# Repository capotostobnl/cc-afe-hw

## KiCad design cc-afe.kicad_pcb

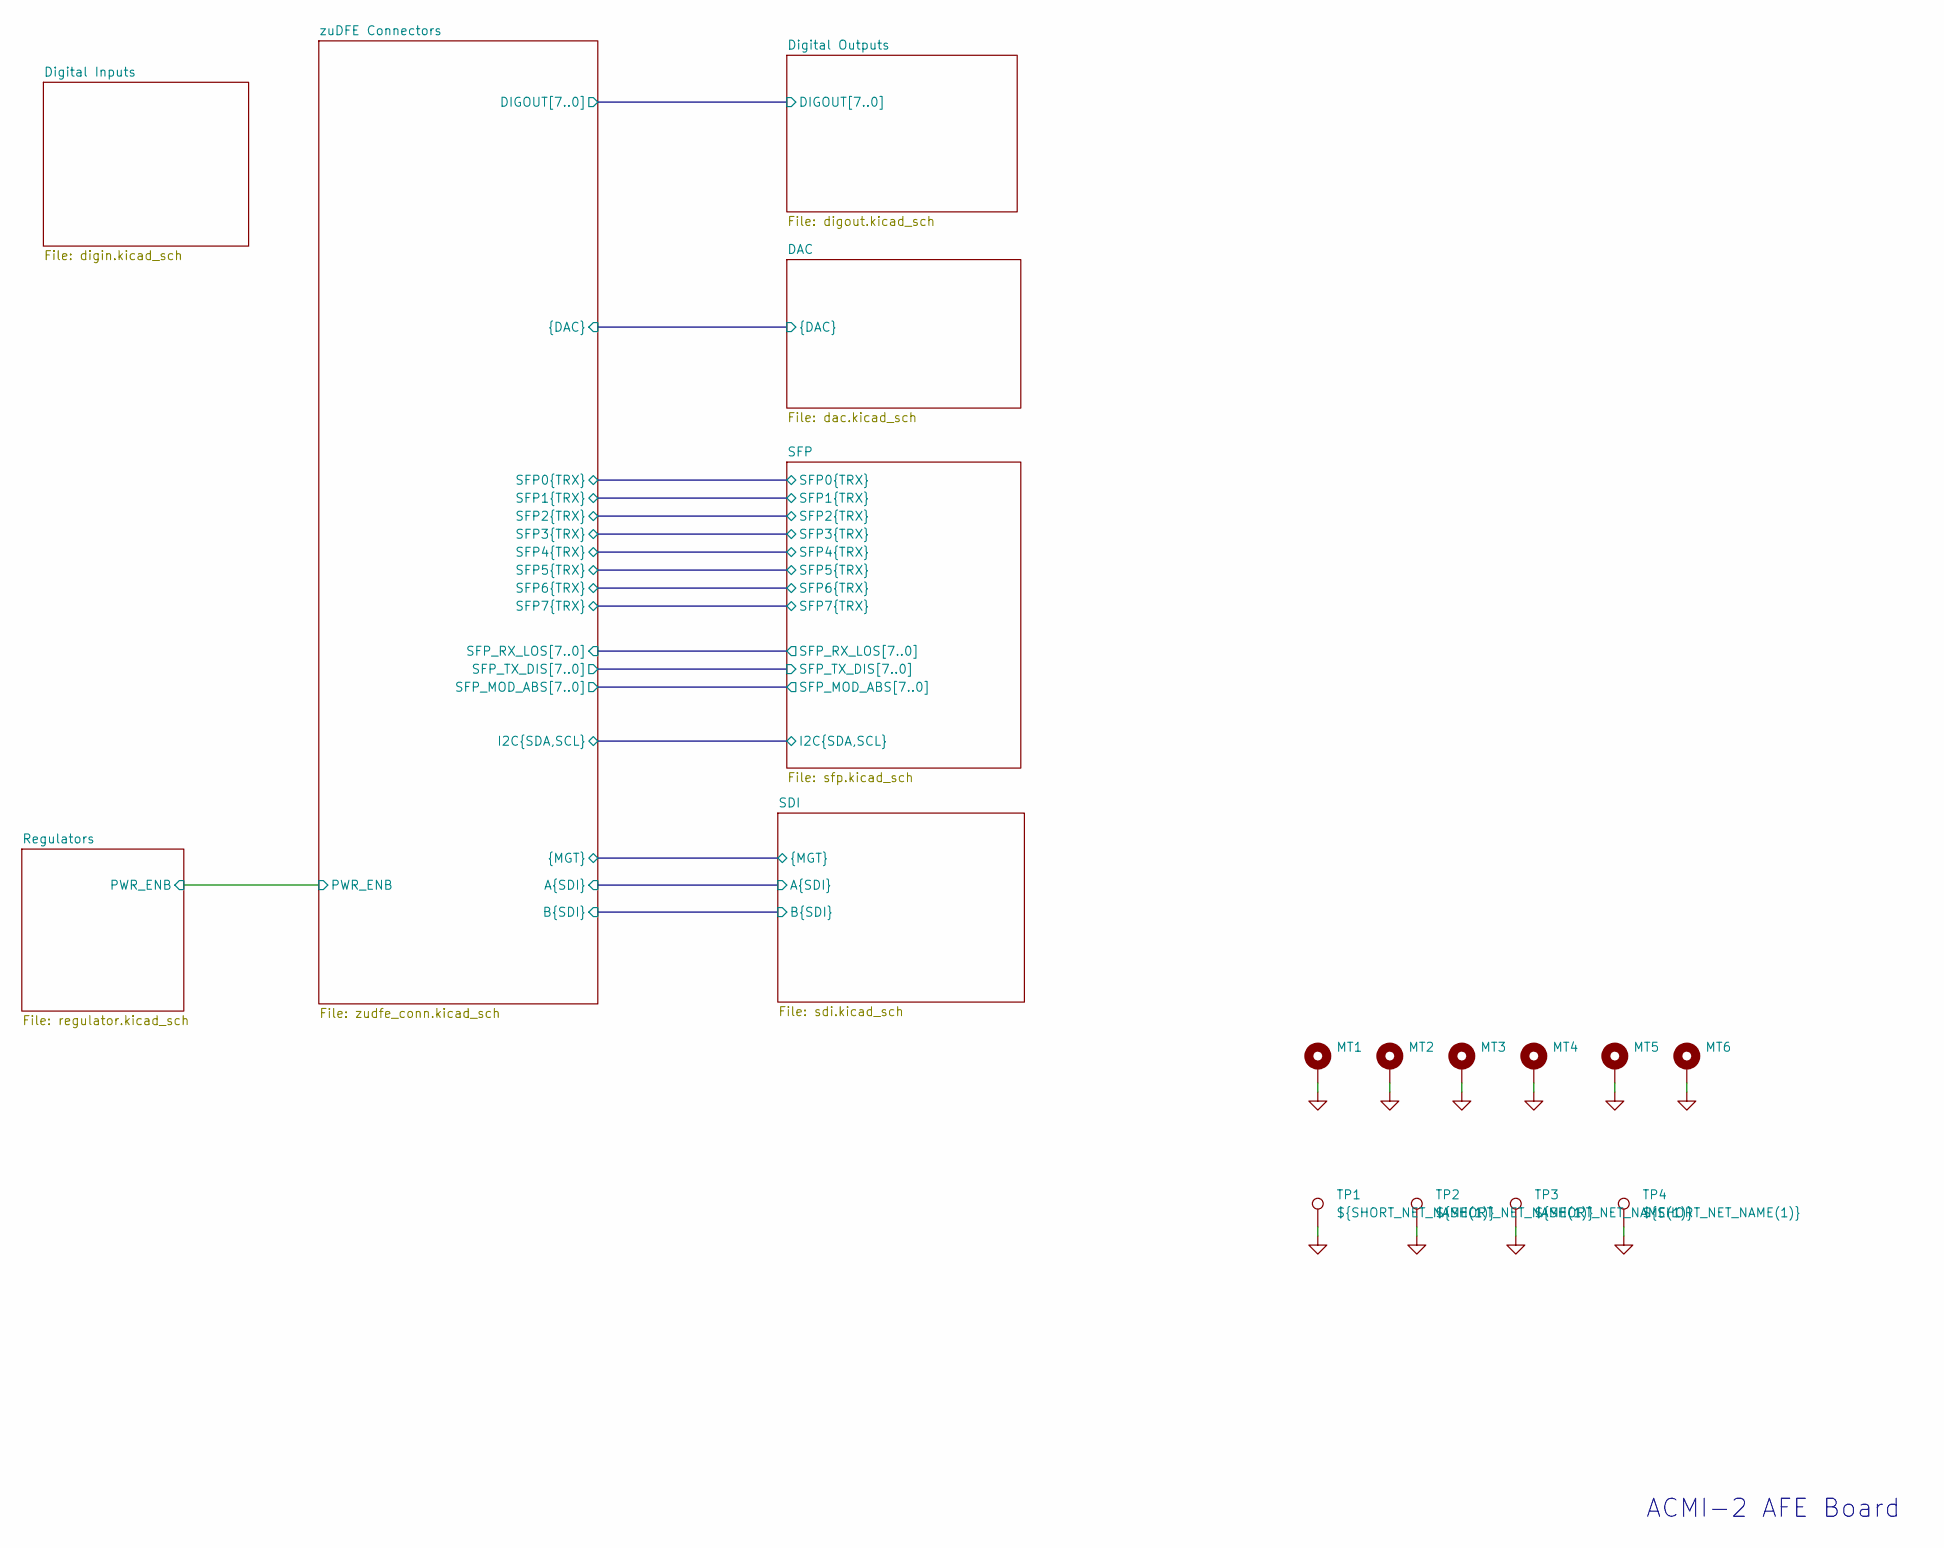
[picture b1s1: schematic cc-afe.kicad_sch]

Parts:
MT1, MT2, MT3, MT4, MT5, MT6: MountingHole_Pad; MountingHole_4.3mm_M4_DIN965_Pad
TP1, TP2, TP3, TP4: ${SHORT_NET_NAME(1)}; TestPoint_RCS-0C; MFG_PN RCS-0C

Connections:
GND: MT1.1, MT2.1, MT3.1, MT4.1, MT5.1, MT6.1, TP1.1, TP2.1, TP3.1, TP4.1; also elsewhere on the board

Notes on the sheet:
ACMI-2 AFE Board

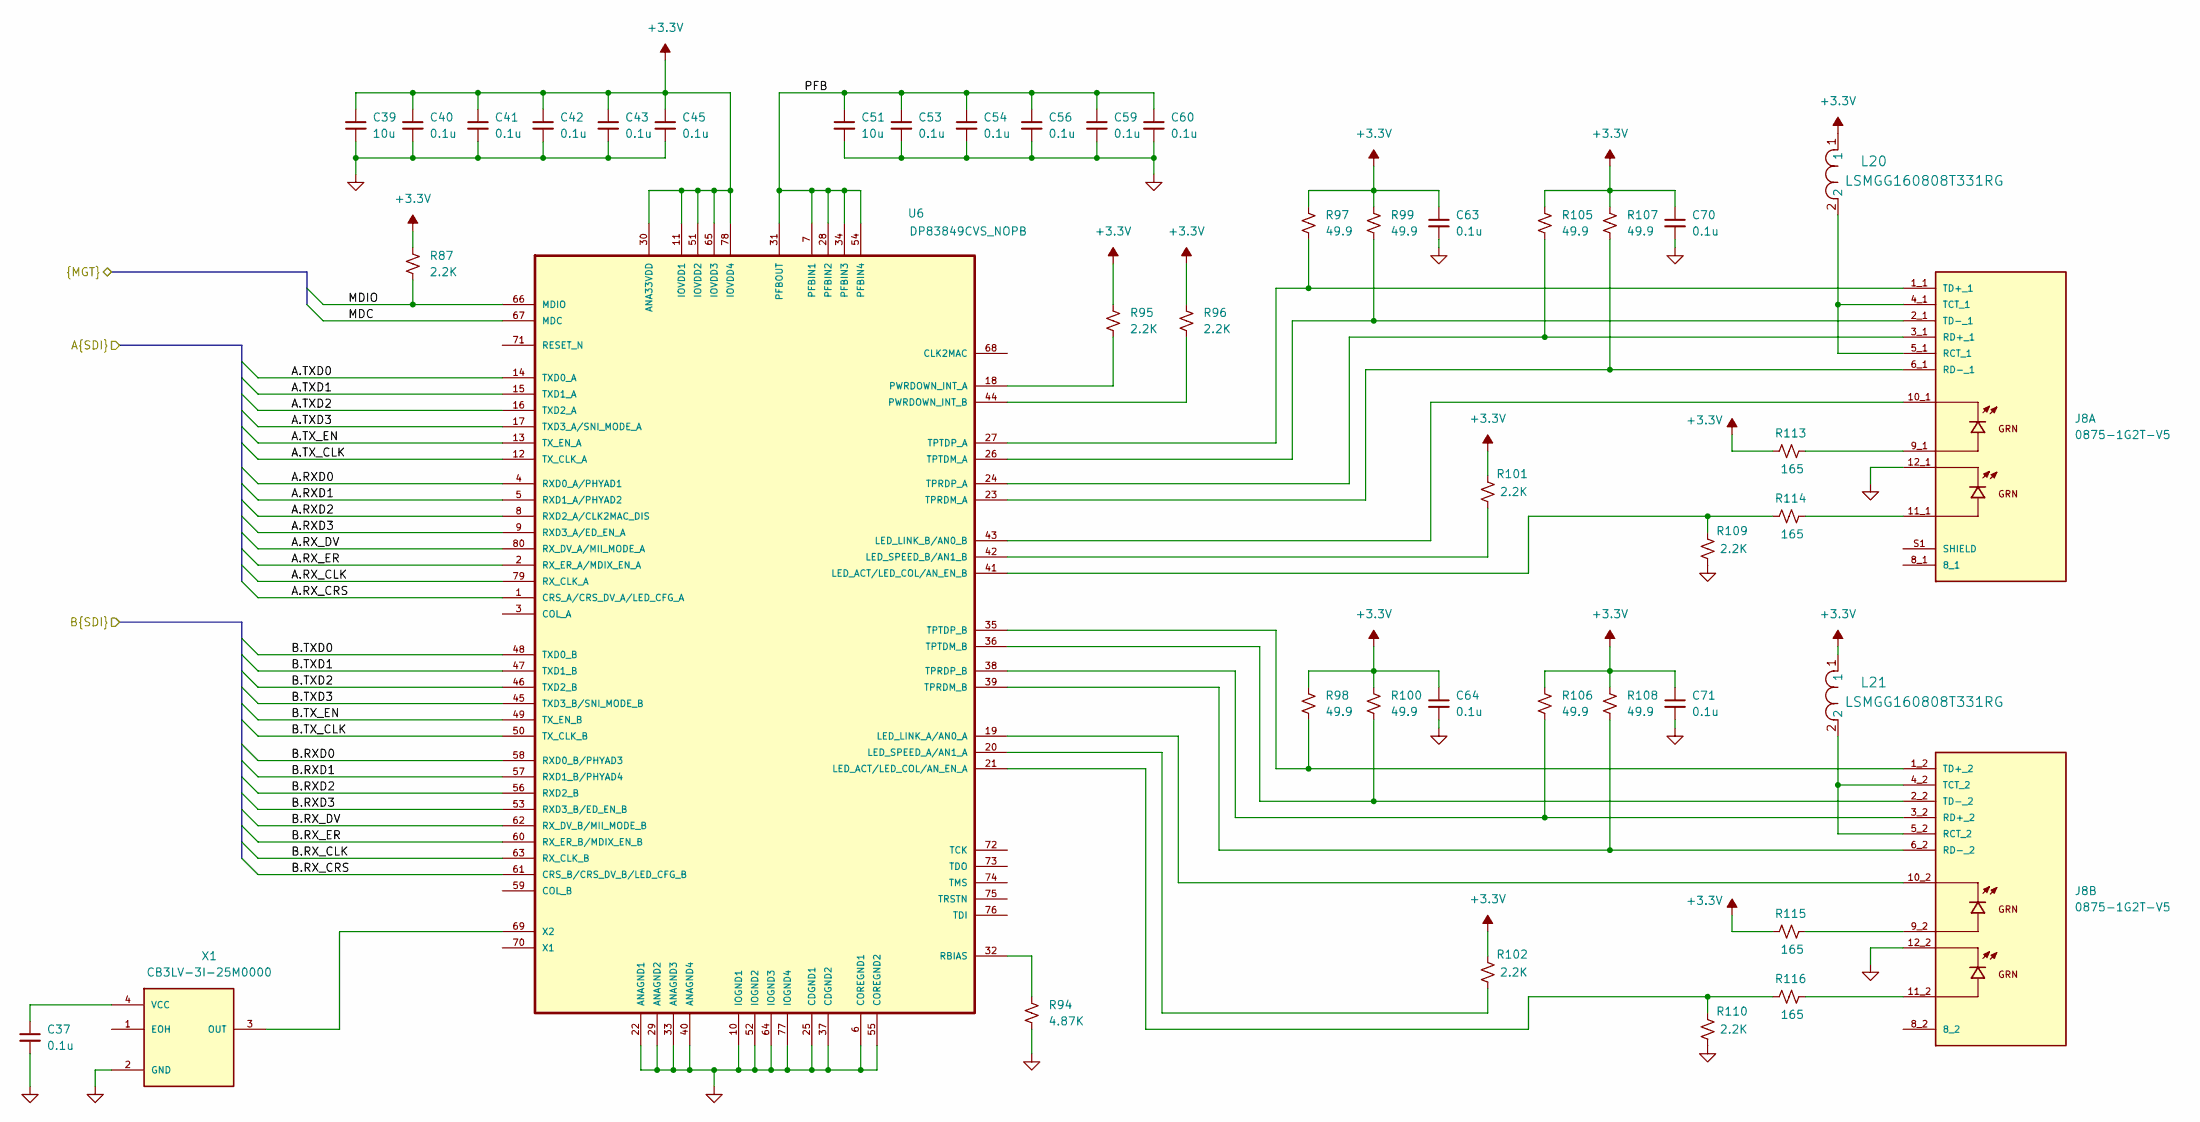
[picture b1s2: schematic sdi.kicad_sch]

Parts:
C37, C40, C41, C42, C43, C45, C53, C54, C56, C59, C60, C63, C64, C70, C71: 0.1u; C_0603_1608Metric; Voltage 50; MFG_PN GCJ188R71H104KA12D
C39, C51: 10u; C_0805_2012Metric; MFG_PN GRM21BR61C106KE15K
J8: 0875-1G2T-V5; BEL_0875-1G2T-V5
L20, L21: LSMGG160808T331RG; IND_LSMG_160808_TAY; MFG_PN LSMGG160808T331RG
R87, R95, R96: 2.2K; R_0603_1608Metric; MFG_PN ERJ-3EKF49R9V
R94: 4.87K; R_0603_1608Metric
R97, R98, R99, R100, R105, R106, R107, R108: 49.9; R_0603_1608Metric; MFG_PN ERJ-3EKF49R9V
R101, R102, R109, R110: 2.2K; R_0603_1608Metric
R113, R114, R115, R116: 165; R_0603_1608Metric
U6: DP83849CVS_NOPB; QFP50P1400X1400X120-80N; MFG_PN DP83849CVS/NOPB
X1: CB3LV-3I-25M0000; OSCCC700X500X180-4N; MFG_PN CB3LV-3I-25M0000

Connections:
+3.3V: C39.1, C40.1, C41.1, C42.1, C43.1, C45.1, C63.1, C64.1, C70.1, C71.1, L20.1, L21.1, R87.1, R95.1, R96.1, R97.1, R98.1, R99.1, R100.1, R101.2, R102.2, R105.1, R106.1, R107.1, R108.1, R113.1, R115.1, U6.11 (IOVDD1), U6.30 (ANA33VDD), U6.51 (IOVDD2), U6.65 (IOVDD3), U6.78 (IOVDD4); also elsewhere on the board
/SDI/A.RXD0: U6.4 (RXD0_A/PHYAD1); also elsewhere on the board
/SDI/A.RXD1: U6.5 (RXD1_A/PHYAD2); also elsewhere on the board
/SDI/A.RXD2: U6.8 (RXD2_A/CLK2MAC_DIS); also elsewhere on the board
/SDI/A.RXD3: U6.9 (RXD3_A/ED_EN_A); also elsewhere on the board
/SDI/A.RX_CLK: U6.79 (RX_CLK_A); also elsewhere on the board
/SDI/A.RX_CRS: U6.1 (CRS_A/CRS_DV_A/LED_CFG_A); also elsewhere on the board
/SDI/A.RX_DV: U6.80 (RX_DV_A/MII_MODE_A); also elsewhere on the board
/SDI/A.RX_ER: U6.2 (RX_ER_A/MDIX_EN_A); also elsewhere on the board
/SDI/A.TXD0: U6.14 (TXD0_A); also elsewhere on the board
/SDI/A.TXD1: U6.15 (TXD1_A); also elsewhere on the board
/SDI/A.TXD2: U6.16 (TXD2_A); also elsewhere on the board
/SDI/A.TXD3: U6.17 (TXD3_A/SNI_MODE_A); also elsewhere on the board
/SDI/A.TX_CLK: U6.12 (TX_CLK_A); also elsewhere on the board
/SDI/A.TX_EN: U6.13 (TX_EN_A); also elsewhere on the board
/SDI/B.RXD0: U6.58 (RXD0_B/PHYAD3); also elsewhere on the board
/SDI/B.RXD1: U6.57 (RXD1_B/PHYAD4); also elsewhere on the board
/SDI/B.RXD2: U6.56 (RXD2_B); also elsewhere on the board
/SDI/B.RXD3: U6.53 (RXD3_B/ED_EN_B); also elsewhere on the board
/SDI/B.RX_CLK: U6.63 (RX_CLK_B); also elsewhere on the board
/SDI/B.RX_CRS: U6.61 (CRS_B/CRS_DV_B/LED_CFG_B); also elsewhere on the board
/SDI/B.RX_DV: U6.62 (RX_DV_B/MII_MODE_B); also elsewhere on the board
/SDI/B.RX_ER: U6.60 (RX_ER_B/MDIX_EN_B); also elsewhere on the board
/SDI/B.TXD0: U6.48 (TXD0_B); also elsewhere on the board
/SDI/B.TXD1: U6.47 (TXD1_B); also elsewhere on the board
/SDI/B.TXD2: U6.46 (TXD2_B); also elsewhere on the board
/SDI/B.TXD3: U6.45 (TXD3_B/SNI_MODE_B); also elsewhere on the board
/SDI/B.TX_CLK: U6.50 (TX_CLK_B); also elsewhere on the board
/SDI/B.TX_EN: U6.49 (TX_EN_B); also elsewhere on the board
/SDI/MDC: U6.67 (MDC); also elsewhere on the board
/SDI/MDIO: R87.2, U6.66 (MDIO); also elsewhere on the board
/SDI/PFB: C51.1, C53.1, C54.1, C56.1, C59.1, C60.1, U6.7 (PFBIN1), U6.28 (PFBIN2), U6.31 (PFBOUT), U6.34 (PFBIN3), U6.54 (PFBIN4)
GND: C37.2, C39.2, C40.2, C41.2, C42.2, C43.2, C45.2, C51.2, C53.2, C54.2, C56.2, C59.2, C60.2, C63.2, C64.2, C70.2, C71.2, J8.12_1, J8.12_2, R94.2, R109.1, R110.1, U6.6 (COREGND1), U6.10 (IOGND1), U6.22 (ANAGND1), U6.25 (CDGND1), U6.29 (ANAGND2), U6.33 (ANAGND3), U6.37 (CDGND2), U6.40 (ANAGND4), U6.52 (IOGND2), U6.55 (COREGND2), U6.64 (IOGND3), U6.77 (IOGND4), X1.2 (GND); also elsewhere on the board
unnamed: J8.9_1, R113.2
unnamed: J8.9_2, R115.2
unnamed: J8.11_1, R114.2
unnamed: J8.11_2, R116.2
unnamed: J8.4_1 (TCT_1), J8.5_1 (RCT_1), L20.2
unnamed: J8.3_1 (RD+_1), R105.2, U6.24 (TPRDP_A)
unnamed: J8.6_1 (RD-_1), R107.2, U6.23 (TPRDM_A)
unnamed: J8.S1 (SHIELD), J8.S2 (SHIELD), J8.S3 (SHIELD)
unnamed: J8.1_1 (TD+_1), R97.2, U6.27 (TPTDP_A)
unnamed: J8.2_1 (TD-_1), R99.2, U6.26 (TPTDM_A)
unnamed: J8.4_2 (TCT_2), J8.5_2 (RCT_2), L21.2
unnamed: J8.3_2 (RD+_2), R106.2, U6.38 (TPRDP_B)
unnamed: J8.6_2 (RD-_2), R108.2, U6.39 (TPRDM_B)
unnamed: J8.1_2 (TD+_2), R98.2, U6.35 (TPTDP_B)
unnamed: J8.2_2 (TD-_2), R100.2, U6.36 (TPTDM_B)
unnamed: R110.2, R116.1, U6.21 (LED_ACT/LED_COL/AN_EN_A)
unnamed: R109.2, R114.1, U6.41 (LED_ACT/LED_COL/AN_EN_B)
unnamed: J8.10_2, U6.19 (LED_LINK_A/AN0_A)
unnamed: J8.10_1, U6.43 (LED_LINK_B/AN0_B)
unnamed: R102.1, U6.20 (LED_SPEED_A/AN1_A)
unnamed: R101.1, U6.42 (LED_SPEED_B/AN1_B)
unnamed: R95.2, U6.18 (PWRDOWN_INT_A)
unnamed: R96.2, U6.44 (PWRDOWN_INT_B)
unnamed: R94.1, U6.32 (RBIAS)
unnamed: U6.69 (X2), X1.3 (OUT)
unnamed: C37.1, X1.4 (VCC)

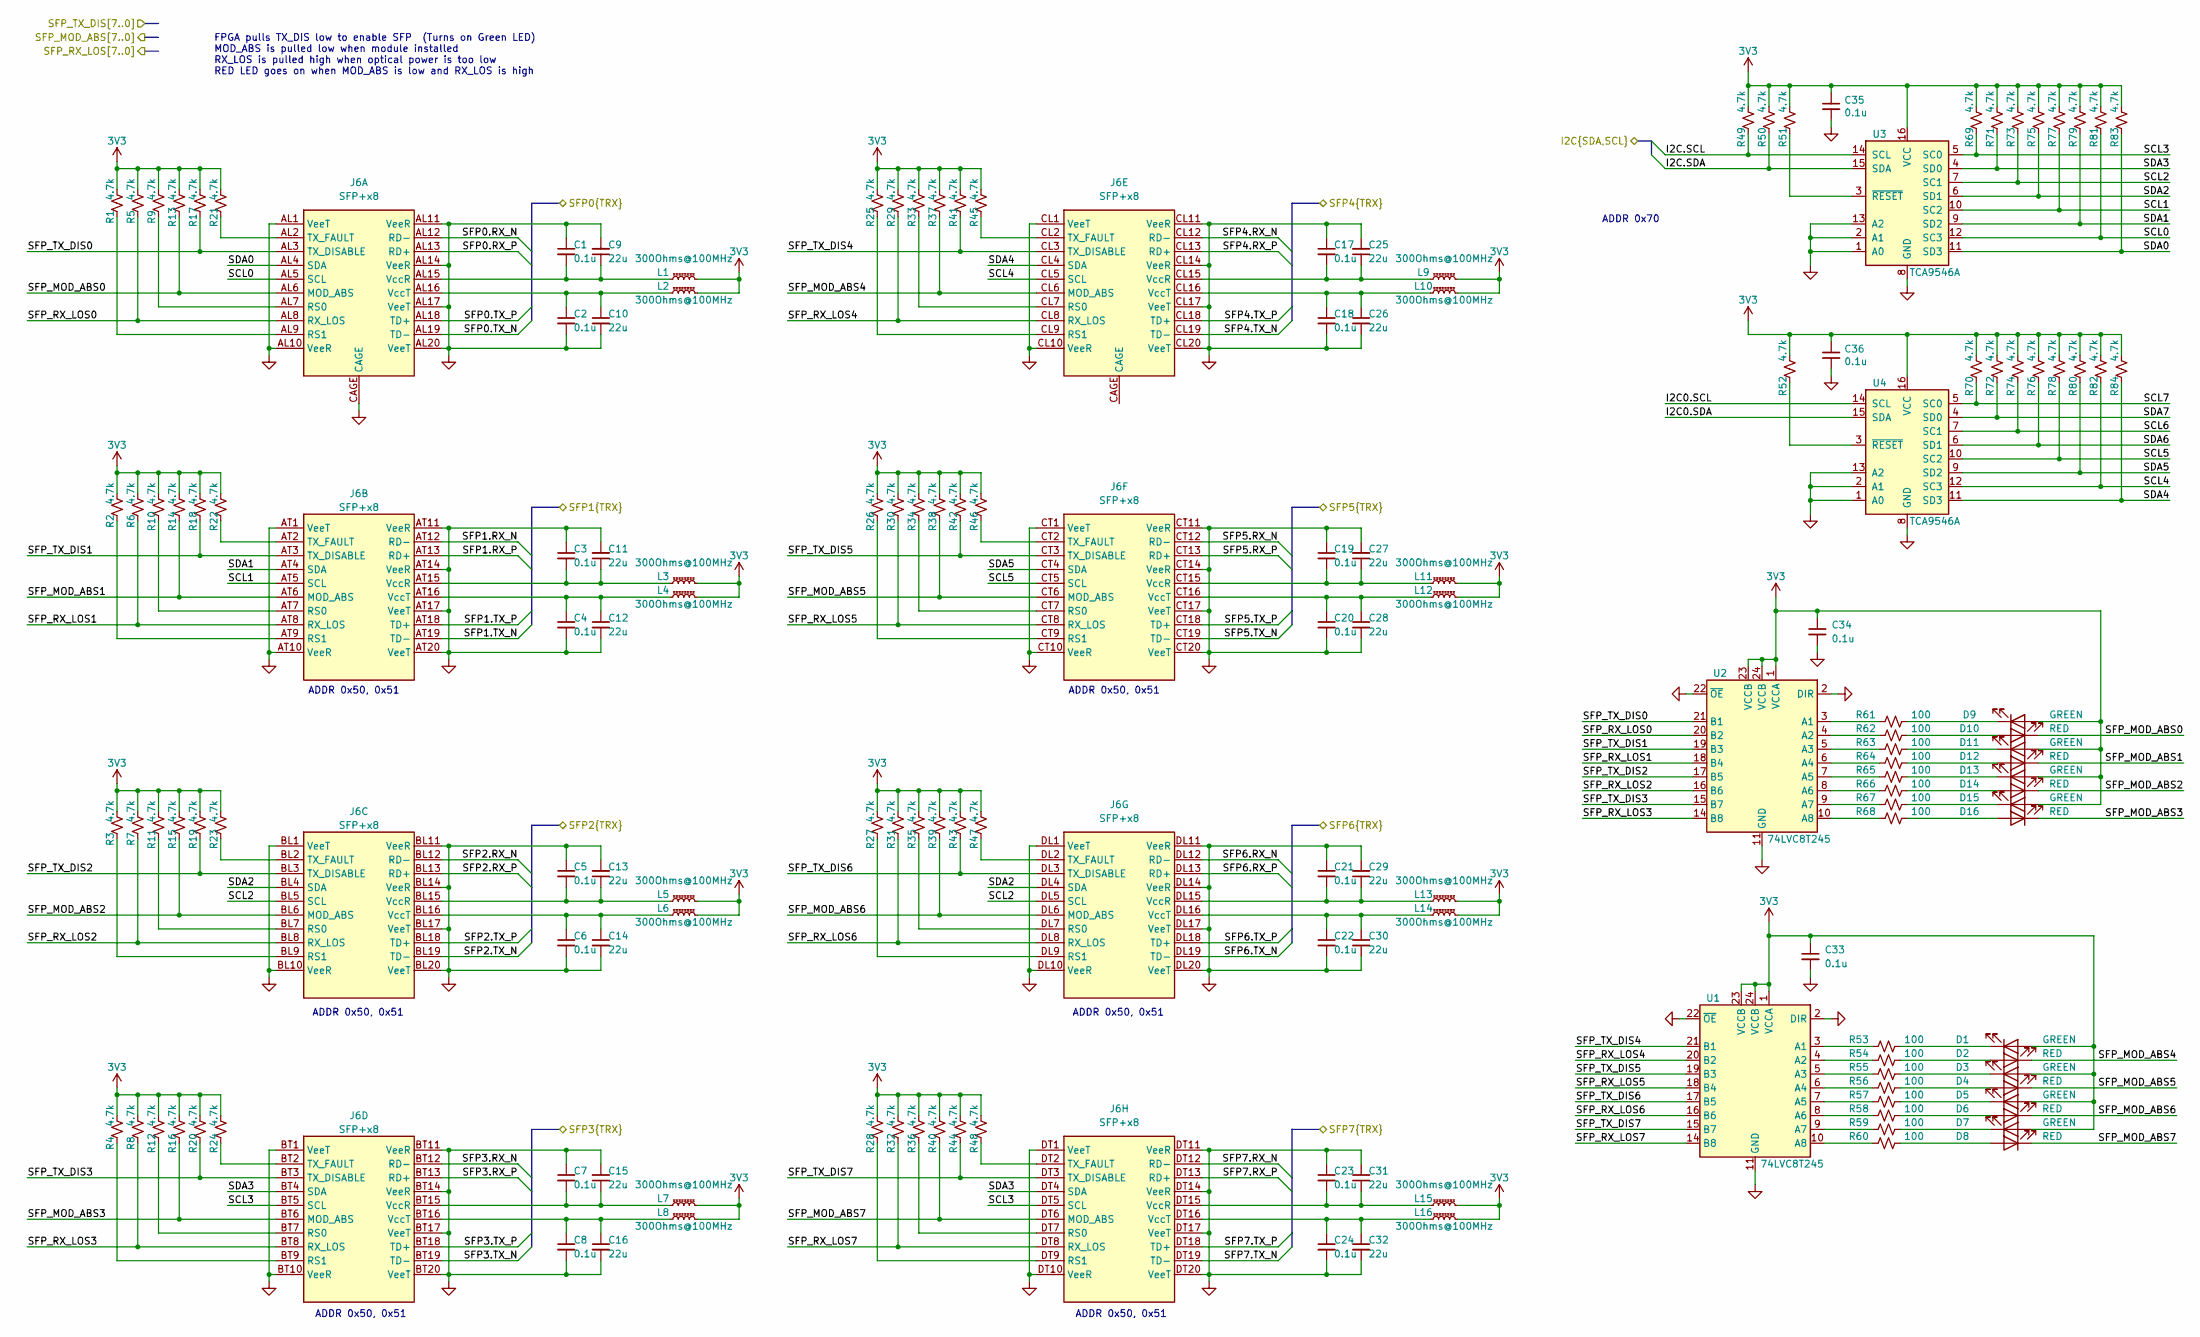
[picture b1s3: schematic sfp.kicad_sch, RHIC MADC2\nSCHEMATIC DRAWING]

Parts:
C1, C2, C3, C4, C5, C6, C7, C8, C17, C18, C19, C20, C21, C22, C23, C24, C33, C34, C35, C36: 0.1u; C_0603_1608Metric; MFG_PN CL10B104KB8NNNC
C9, C10, C11, C12, C13, C14, C15, C16, C25, C26, C27, C28, C29, C30, C31, C32: 22u; C_0805_2012Metric; MFG_PN CL21A226MAYNNNE
D1, D3, D5, D7, D9, D11, D13, D15: GREEN; LED_0603_1608Metric; MFG_PN LTST-C191KGKT
D2, D4, D6, D8, D10, D12, D14, D16: RED; LED_0603_1608Metric; MFG_PN LTST-C191KRKT
J6: SFP+x8; 1-2007394-5
L1, L2, L3, L4, L5, L6, L7, L8, L9, L10, L11, L12, L13, L14, L15, L16: 300Ohms@100MHz; L_0603_1608Metric; MFG_PN 742792641
R1, R2, R3, R4, R5, R6, R7, R8, R9, R10, R11, R12, R13, R14, R15, R16, R17, R18, R19, R20, R21, R22, R23, R24, R25, R26, R27, R28, R29, R30, R31, R32, R33, R34, R35, R36, R37, R38, R39, R40, R41, R42, R43, R44, R45, R46, R47, R48, R49, R50, R51, R52, R69, R70, R71, R72, R73, R74, R75, R76, R77, R78, R79, R80, R81, R82, R83, R84: 4.7k; R_0603_1608Metric; MFG_PN RMCF0603FT4K70
R53, R54, R55, R56, R57, R58, R59, R60, R61, R62, R63, R64, R65, R66, R67, R68: 100; R_0603_1608Metric; MFG_PN RMCF0603FT100R
U1, U2: 74LVC8T245; TSSOP-24_4.4x7.8mm_P0.65mm; MFG_PN 74LVC8T245PW,118
U3, U4: TCA9546A; TSSOP-16_4.4x5mm_P0.65mm; MFG_PN TCA9546APWR

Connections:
3V3: C33.1, C34.1, C35.1, C36.1, D1.2 (A), D3.2 (A), D5.2 (A), D7.2 (A), D9.2 (A), D11.2 (A), D13.2 (A), D15.2 (A), L1.1, L2.1, L3.1, L4.1, L5.1, L6.1, L7.1, L8.1, L9.1, L10.1, L11.1, L12.1, L13.1, L14.1, L15.1, L16.1, R1.2, R2.2, R3.2, R4.2, R5.2, R6.2, R7.2, R8.2, R9.2, R10.2, R11.2, R12.2, R13.2, R14.2, R15.2, R16.2, R17.2, R18.2, R19.2, R20.2, R21.2, R22.2, R23.2, R24.2, R25.2, R26.2, R27.2, R28.2, R29.2, R30.2, R31.2, R32.2, R33.2, R34.2, R35.2, R36.2, R37.2, R38.2, R39.2, R40.2, R41.2, R42.2, R43.2, R44.2, R45.2, R46.2, R47.2, R48.2, R49.1, R50.1, R51.1, R52.1, R69.1, R70.1, R71.1, R72.1, R73.1, R74.1, R75.1, R76.1, R77.1, R78.1, R79.1, R80.1, R81.1, R82.1, R83.1, R84.1, U1.1 (VCCA), U1.23 (VCCB), U1.24 (VCCB), U2.1 (VCCA), U2.23 (VCCB), U2.24 (VCCB), U3.16 (VCC), U4.16 (VCC)
/SFP/I2C0.SCL: U4.14 (SCL)
/SFP/I2C0.SDA: U4.15 (SDA)
/SFP/I2C.SCL: R49.2, U3.14 (SCL); also elsewhere on the board
/SFP/I2C.SDA: R50.2, U3.15 (SDA); also elsewhere on the board
/SFP/SCL0: J6.AL5 (SCL), R81.2, U3.12 (SC3)
/SFP/SCL1: J6.AT5 (SCL), R77.2, U3.10 (SC2)
/SFP/SCL2: J6.BL5 (SCL), J6.DL5 (SCL), R73.2, U3.7 (SC1)
/SFP/SCL3: J6.BT5 (SCL), J6.DT5 (SCL), R69.2, U3.5 (SC0)
/SFP/SCL4: J6.CL5 (SCL), R82.2, U4.12 (SC3)
/SFP/SCL5: J6.CT5 (SCL), R78.2, U4.10 (SC2)
/SFP/SCL6: R74.2, U4.7 (SC1)
/SFP/SCL7: R70.2, U4.5 (SC0)
/SFP/SDA0: J6.AL4 (SDA), R83.2, U3.11 (SD3)
/SFP/SDA1: J6.AT4 (SDA), R79.2, U3.9 (SD2)
/SFP/SDA2: J6.BL4 (SDA), J6.DL4 (SDA), R75.2, U3.6 (SD1)
/SFP/SDA3: J6.BT4 (SDA), J6.DT4 (SDA), R71.2, U3.4 (SD0)
/SFP/SDA4: J6.CL4 (SDA), R84.2, U4.11 (SD3)
/SFP/SDA5: J6.CT4 (SDA), R80.2, U4.9 (SD2)
/SFP/SDA6: R76.2, U4.6 (SD1)
/SFP/SDA7: R72.2, U4.4 (SD0)
/SFP/SFP0.RX_N: J6.AL12 (RD-); also elsewhere on the board
/SFP/SFP0.RX_P: J6.AL13 (RD+); also elsewhere on the board
/SFP/SFP0.TX_N: J6.AL19 (TD-); also elsewhere on the board
/SFP/SFP0.TX_P: J6.AL18 (TD+); also elsewhere on the board
/SFP/SFP1.RX_N: J6.AT12 (RD-); also elsewhere on the board
/SFP/SFP1.RX_P: J6.AT13 (RD+); also elsewhere on the board
/SFP/SFP1.TX_N: J6.AT19 (TD-); also elsewhere on the board
/SFP/SFP1.TX_P: J6.AT18 (TD+); also elsewhere on the board
/SFP/SFP2.RX_N: J6.BL12 (RD-); also elsewhere on the board
/SFP/SFP2.RX_P: J6.BL13 (RD+); also elsewhere on the board
/SFP/SFP2.TX_N: J6.BL19 (TD-); also elsewhere on the board
/SFP/SFP2.TX_P: J6.BL18 (TD+); also elsewhere on the board
/SFP/SFP3.RX_N: J6.BT12 (RD-); also elsewhere on the board
/SFP/SFP3.RX_P: J6.BT13 (RD+); also elsewhere on the board
/SFP/SFP3.TX_N: J6.BT19 (TD-); also elsewhere on the board
/SFP/SFP3.TX_P: J6.BT18 (TD+); also elsewhere on the board
/SFP/SFP4.RX_N: J6.CL12 (RD-); also elsewhere on the board
/SFP/SFP4.RX_P: J6.CL13 (RD+); also elsewhere on the board
/SFP/SFP4.TX_N: J6.CL19 (TD-); also elsewhere on the board
/SFP/SFP4.TX_P: J6.CL18 (TD+); also elsewhere on the board
/SFP/SFP5.RX_N: J6.CT12 (RD-); also elsewhere on the board
/SFP/SFP5.RX_P: J6.CT13 (RD+); also elsewhere on the board
/SFP/SFP5.TX_N: J6.CT19 (TD-); also elsewhere on the board
/SFP/SFP5.TX_P: J6.CT18 (TD+); also elsewhere on the board
/SFP/SFP6.RX_N: J6.DL12 (RD-); also elsewhere on the board
/SFP/SFP6.RX_P: J6.DL13 (RD+); also elsewhere on the board
/SFP/SFP6.TX_N: J6.DL19 (TD-); also elsewhere on the board
/SFP/SFP6.TX_P: J6.DL18 (TD+); also elsewhere on the board
/SFP/SFP7.RX_N: J6.DT12 (RD-); also elsewhere on the board
/SFP/SFP7.RX_P: J6.DT13 (RD+); also elsewhere on the board
/SFP/SFP7.TX_N: J6.DT19 (TD-); also elsewhere on the board
/SFP/SFP7.TX_P: J6.DT18 (TD+); also elsewhere on the board
/SFP/SFP_MOD_ABS0: D10.1 (K), J6.AL6 (MOD_ABS), R13.1; also elsewhere on the board
/SFP/SFP_MOD_ABS1: D12.1 (K), J6.AT6 (MOD_ABS), R14.1; also elsewhere on the board
/SFP/SFP_MOD_ABS2: D14.1 (K), J6.BL6 (MOD_ABS), R15.1; also elsewhere on the board
/SFP/SFP_MOD_ABS3: D16.1 (K), J6.BT6 (MOD_ABS), R16.1; also elsewhere on the board
/SFP/SFP_MOD_ABS4: D2.1 (K), J6.CL6 (MOD_ABS), R37.1; also elsewhere on the board
/SFP/SFP_MOD_ABS5: D4.1 (K), J6.CT6 (MOD_ABS), R38.1; also elsewhere on the board
/SFP/SFP_MOD_ABS6: D6.1 (K), J6.DL6 (MOD_ABS), R39.1; also elsewhere on the board
/SFP/SFP_MOD_ABS7: D8.1 (K), J6.DT6 (MOD_ABS), R40.1; also elsewhere on the board
/SFP/SFP_RX_LOS0: J6.AL8 (RX_LOS), R5.1, U2.20 (B2); also elsewhere on the board
/SFP/SFP_RX_LOS1: J6.AT8 (RX_LOS), R6.1, U2.18 (B4); also elsewhere on the board
/SFP/SFP_RX_LOS2: J6.BL8 (RX_LOS), R7.1, U2.16 (B6); also elsewhere on the board
/SFP/SFP_RX_LOS3: J6.BT8 (RX_LOS), R8.1, U2.14 (B8); also elsewhere on the board
/SFP/SFP_RX_LOS4: J6.CL8 (RX_LOS), R29.1, U1.20 (B2); also elsewhere on the board
/SFP/SFP_RX_LOS5: J6.CT8 (RX_LOS), R30.1, U1.18 (B4); also elsewhere on the board
/SFP/SFP_RX_LOS6: J6.DL8 (RX_LOS), R31.1, U1.16 (B6); also elsewhere on the board
/SFP/SFP_RX_LOS7: J6.DT8 (RX_LOS), R32.1, U1.14 (B8); also elsewhere on the board
/SFP/SFP_TX_DIS0: J6.AL3 (TX_DISABLE), R17.1, U2.21 (B1); also elsewhere on the board
/SFP/SFP_TX_DIS1: J6.AT3 (TX_DISABLE), R18.1, U2.19 (B3); also elsewhere on the board
/SFP/SFP_TX_DIS2: J6.BL3 (TX_DISABLE), R19.1, U2.17 (B5); also elsewhere on the board
/SFP/SFP_TX_DIS3: J6.BT3 (TX_DISABLE), R20.1, U2.15 (B7); also elsewhere on the board
/SFP/SFP_TX_DIS4: J6.CL3 (TX_DISABLE), R41.1, U1.21 (B1); also elsewhere on the board
/SFP/SFP_TX_DIS5: J6.CT3 (TX_DISABLE), R42.1, U1.19 (B3); also elsewhere on the board
/SFP/SFP_TX_DIS6: J6.DL3 (TX_DISABLE), R43.1, U1.17 (B5); also elsewhere on the board
/SFP/SFP_TX_DIS7: J6.DT3 (TX_DISABLE), R44.1, U1.15 (B7); also elsewhere on the board
GND: C1.1, C2.2, C3.1, C4.2, C5.1, C6.2, C7.1, C8.2, C9.2, C10.2, C11.2, C12.2, C13.2, C14.2, C15.2, C16.2, C17.1, C18.2, C19.1, C20.2, C21.1, C22.2, C23.1, C24.2, C25.2, C26.2, C27.2, C28.2, C29.2, C30.2, C31.2, C32.2, C33.2, C34.2, C35.2, C36.2, J6.AL1 (VeeT), J6.AL10 (VeeR), J6.AL11 (VeeR), J6.AL14 (VeeR), J6.AL17 (VeeT), J6.AL20 (VeeT), J6.AT1 (VeeT), J6.AT10 (VeeR), J6.AT11 (VeeR), J6.AT14 (VeeR), J6.AT17 (VeeT), J6.AT20 (VeeT), J6.BL1 (VeeT), J6.BL10 (VeeR), J6.BL11 (VeeR), J6.BL14 (VeeR), J6.BL17 (VeeT), J6.BL20 (VeeT), J6.BT1 (VeeT), J6.BT10 (VeeR), J6.BT11 (VeeR), J6.BT14 (VeeR), J6.BT17 (VeeT), J6.BT20 (VeeT), J6.CAGE, J6.CL1 (VeeT), J6.CL10 (VeeR), J6.CL11 (VeeR), J6.CL14 (VeeR), J6.CL17 (VeeT), J6.CL20 (VeeT), J6.CT1 (VeeT), J6.CT10 (VeeR), J6.CT11 (VeeR), J6.CT14 (VeeR), J6.CT17 (VeeT), J6.CT20 (VeeT), J6.DL1 (VeeT), J6.DL10 (VeeR), J6.DL11 (VeeR), J6.DL14 (VeeR), J6.DL17 (VeeT), J6.DL20 (VeeT), J6.DT1 (VeeT), J6.DT10 (VeeR), J6.DT11 (VeeR), J6.DT14 (VeeR), J6.DT17 (VeeT), J6.DT20 (VeeT), U1.2 (DIR), U1.11 (GND), U1.12 (GND), U1.13 (GND), U1.22 (~OE), U2.2 (DIR), U2.11 (GND), U2.12 (GND), U2.13 (GND), U2.22 (~OE), U3.1 (A0), U3.2 (A1), U3.8 (GND), U3.13 (A2), U4.1 (A0), U4.2 (A1), U4.8 (GND), U4.13 (A2); also elsewhere on the board
unnamed: D1.1 (K), R53.2
unnamed: D2.2 (A), R54.2
unnamed: D3.1 (K), R55.2
unnamed: D4.2 (A), R56.2
unnamed: D5.1 (K), R57.2
unnamed: D6.2 (A), R58.2
unnamed: D7.1 (K), R59.2
unnamed: D8.2 (A), R60.2
unnamed: D9.1 (K), R61.2
unnamed: D10.2 (A), R62.2
unnamed: D11.1 (K), R63.2
unnamed: D12.2 (A), R64.2
unnamed: D13.1 (K), R65.2
unnamed: D14.2 (A), R66.2
unnamed: D15.1 (K), R67.2
unnamed: D16.2 (A), R68.2
unnamed: J6.AL7 (RS0), R9.1
unnamed: J6.AL9 (RS1), R1.1
unnamed: J6.AL2 (TX_FAULT), R21.1
unnamed: C1.2, C9.1, J6.AL15 (VccR), L1.2
unnamed: C2.1, C10.1, J6.AL16 (VccT), L2.2
unnamed: J6.AT7 (RS0), R10.1
unnamed: J6.AT9 (RS1), R2.1
unnamed: J6.AT2 (TX_FAULT), R22.1
unnamed: C3.2, C11.1, J6.AT15 (VccR), L3.2
unnamed: C4.1, C12.1, J6.AT16 (VccT), L4.2
unnamed: J6.BL7 (RS0), R11.1
unnamed: J6.BL9 (RS1), R3.1
unnamed: J6.BL2 (TX_FAULT), R23.1
unnamed: C5.2, C13.1, J6.BL15 (VccR), L5.2
unnamed: C6.1, C14.1, J6.BL16 (VccT), L6.2
unnamed: J6.BT7 (RS0), R12.1
unnamed: J6.BT9 (RS1), R4.1
unnamed: J6.BT2 (TX_FAULT), R24.1
unnamed: C7.2, C15.1, J6.BT15 (VccR), L7.2
unnamed: C8.1, C16.1, J6.BT16 (VccT), L8.2
unnamed: J6.CL7 (RS0), R33.1
unnamed: J6.CL9 (RS1), R25.1
unnamed: J6.CL2 (TX_FAULT), R45.1
unnamed: C17.2, C25.1, J6.CL15 (VccR), L9.2
unnamed: C18.1, C26.1, J6.CL16 (VccT), L10.2
unnamed: J6.CT7 (RS0), R34.1
unnamed: J6.CT9 (RS1), R26.1
unnamed: J6.CT2 (TX_FAULT), R46.1
unnamed: C19.2, C27.1, J6.CT15 (VccR), L11.2
unnamed: C20.1, C28.1, J6.CT16 (VccT), L12.2
unnamed: J6.DL7 (RS0), R35.1
unnamed: J6.DL9 (RS1), R27.1
unnamed: J6.DL2 (TX_FAULT), R47.1
unnamed: C21.2, C29.1, J6.DL15 (VccR), L13.2
unnamed: C22.1, C30.1, J6.DL16 (VccT), L14.2
unnamed: J6.DT7 (RS0), R36.1
unnamed: J6.DT9 (RS1), R28.1
unnamed: J6.DT2 (TX_FAULT), R48.1
unnamed: C23.2, C31.1, J6.DT15 (VccR), L15.2
unnamed: C24.1, C32.1, J6.DT16 (VccT), L16.2
unnamed: R53.1, U1.3 (A1)
unnamed: R54.1, U1.4 (A2)
unnamed: R55.1, U1.5 (A3)
unnamed: R56.1, U1.6 (A4)
unnamed: R57.1, U1.7 (A5)
unnamed: R58.1, U1.8 (A6)
unnamed: R59.1, U1.9 (A7)
unnamed: R60.1, U1.10 (A8)
unnamed: R61.1, U2.3 (A1)
unnamed: R62.1, U2.4 (A2)
unnamed: R63.1, U2.5 (A3)
unnamed: R64.1, U2.6 (A4)
unnamed: R65.1, U2.7 (A5)
unnamed: R66.1, U2.8 (A6)
unnamed: R67.1, U2.9 (A7)
unnamed: R68.1, U2.10 (A8)
unnamed: R51.2, U3.3 (~RESET)
unnamed: R52.2, U4.3 (~RESET)

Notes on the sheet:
ADDR 0x50, 0x51
ADDR 0x70
FPGA pulls TX_DIS low to enable SFP (Turns on Green LED) MOD_ABS is pulled low when module installed RX_LOS is pulled high when optical power is too low RED LED goes on when MOD_ABS is low and RX_LOS is high

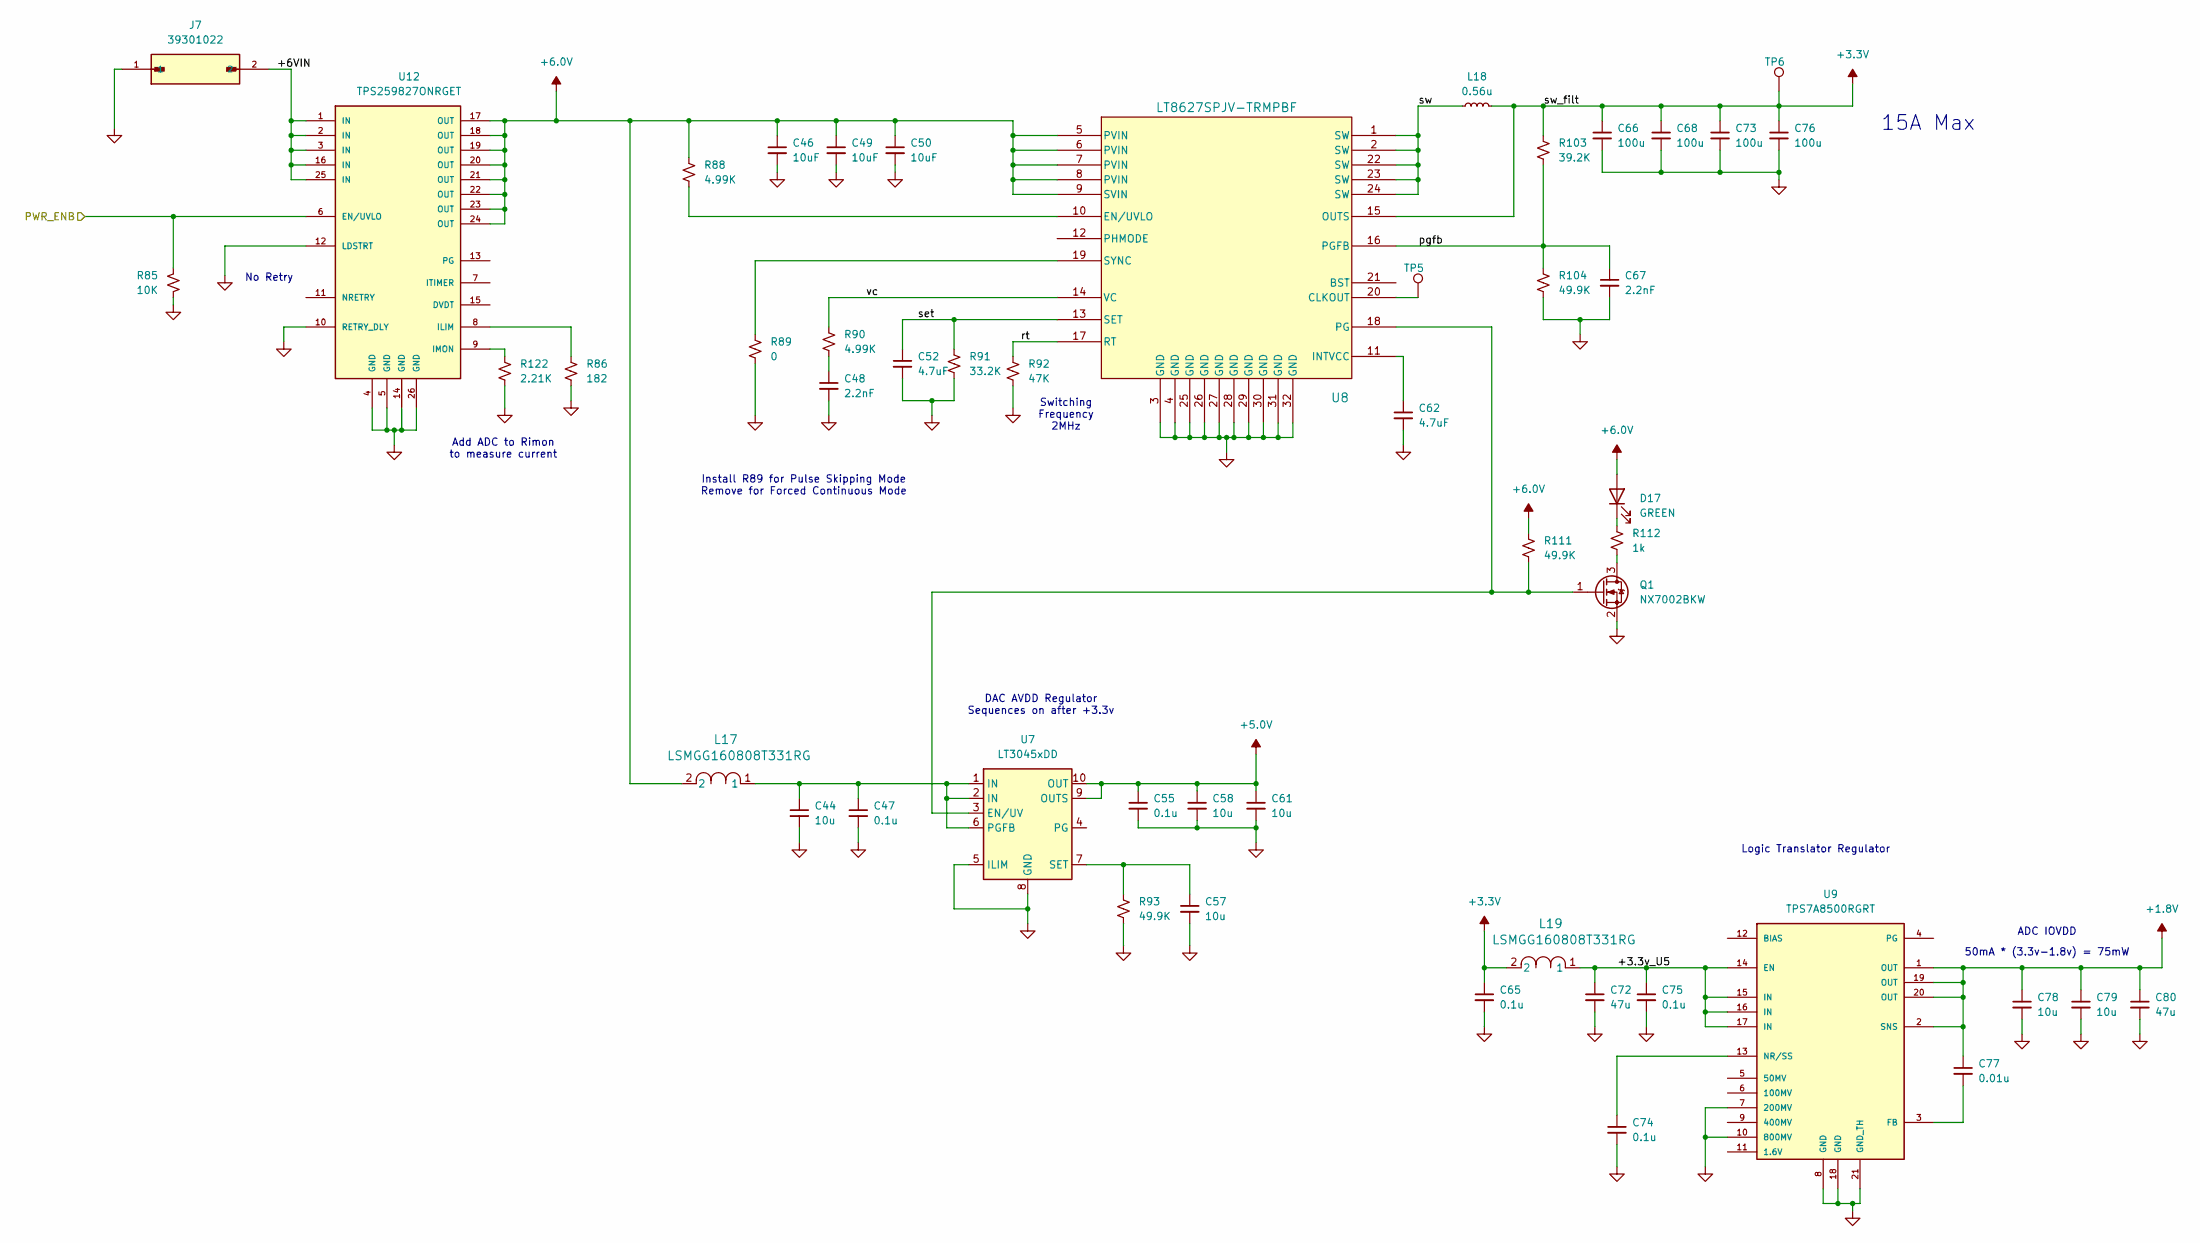
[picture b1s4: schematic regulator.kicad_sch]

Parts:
C44, C57, C58, C61, C78, C79: 10u; C_0805_2012Metric; MFG_PN GRM21BR61C106KE15K
C46, C49, C50: 10uF; C_0603_1608Metric; MFG_PN CL10A106MA8NRNC
C47, C55, C65, C74, C75: 0.1u; C_0805_2012Metric; MFG_PN TMF212B7104KGHT
C48, C67: 2.2nF; C_0603_1608Metric; MFG_PN GCJ188R71E102KA01D
C52: 4.7uF; C_1206_3216Metric; MFG_PN GCM31CR71C475KA37L
C62: 4.7uF; C_0603_1608Metric; MFG_PN GRM188Z71C475KE21D
C66, C68, C73, C76: 100u; C_0805_2012Metric; MFG_PN GRM21BR60J107ME15L
C72, C80: 47u; C_0805_2012Metric; MFG_PN C2012X5R1A476M125AC
C77: 0.01u; C_0805_2012Metric; MFG_PN MAASU21GSL8103MTNA01
D17: GREEN; LED_0603_1608Metric; MFG_PN LTST-C191KGKT
J7: 39301022; MOLEX_39301022; PARTREV A
L17, L19: LSMGG160808T331RG; IND_LSMG_160808_TAY; MFG_PN LSMGG160808T331RG
L18: 0.56u; COILCRAFT_XGL5050; MFG_PN XGL5050-561MEC
Q1: NX7002BKW; SOT-323_SC-70; MFG_PN NX7002BKWX
R85: 10K; R_0805_2012Metric; MFG_PN ERJ-2RKF1001X
R86: 182; R_0805_2012Metric; MFG_PN ERJ-6ENF4700V
R88, R90: 4.99K; R_0603_1608Metric; MFG_PN ERJ-3EKF4991V
R89: 0; R_0603_1608Metric; MFG_PN ERJ-3EKF4991V
R91: 33.2K; R_0603_1608Metric; MFG_PN ERJ-3EKF8661V
R92: 47K; R_0603_1608Metric; MFG_PN ERJ-3EKF4702V
R93: 49.9K; R_0805_2012Metric; MFG_PN ERJ-6ENF2053V
R103: 39.2K; R_0603_1608Metric; MFG_PN ERJ-3EKF3922V
R104, R111: 49.9K; R_0603_1608Metric; MFG_PN ERJ-3EKF4992V
R112: 1k; R_0603_1608Metric; MFG_PN ERJ-3EKF1001V
R122: 2.21K; R_0805_2012Metric; MFG_PN ERJ-6ENF4700V
TP5, TP6: ${SHORT_NET_NAME(1)}; TestPoint_THTPad_D2.0mm_Drill1.0mm
U7: LT3045xDD; DFN-10-1EP_3x3mm_P0.5mm_EP1.65x2.38mm
U8: LT8627SPJV-TRMPBF; 05-08-7039_ADI
U9: TPS7A8500RGRT; QFN50P350X350X100-21N; MFG_PN TPS7A8500RGRT
U12: TPS259827ONRGET; MFG_PN TPS259827ONRGET

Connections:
+1.8V: C77.1, C78.1, C79.1, C80.1, U9.1 (OUT), U9.2 (SNS), U9.19 (OUT), U9.20 (OUT); also elsewhere on the board
+3.3V: C65.1, C66.1, C68.1, C73.1, C76.1, L18.2, L19.2, R103.1, TP6.1, U8.15 (OUTS); also elsewhere on the board
+5.0V: C55.1, C58.1, C61.1, U7.9 (OUTS), U7.10 (OUT); also elsewhere on the board
+6.0V: C46.1, C49.1, C50.1, D17.2 (A), L17.2, R88.1, R111.1, U8.5 (PVIN), U8.6 (PVIN), U8.7 (PVIN), U8.8 (PVIN), U8.9 (SVIN), U12.17 (OUT), U12.18 (OUT), U12.19 (OUT), U12.20 (OUT), U12.21 (OUT), U12.22 (OUT), U12.23 (OUT), U12.24 (OUT)
/Regulators/+3.3v_U5: C72.1, C75.1, L19.1, U9.14 (EN), U9.15 (IN), U9.16 (IN), U9.17 (IN)
/Regulators/+6VIN: J7.2, U12.1 (IN), U12.2 (IN), U12.3 (IN), U12.16 (IN), U12.25 (IN)
/Regulators/PWR_ENB: R85.1, U12.6 (EN/UVLO); also elsewhere on the board
/Regulators/pgfb: C67.1, R103.2, R104.1, U8.16 (PGFB)
/Regulators/rt: R92.1, U8.17 (RT)
/Regulators/set: C52.1, R91.1, U8.13 (SET)
/Regulators/sw: L18.1, U8.1 (SW), U8.2 (SW), U8.22 (SW), U8.23 (SW), U8.24 (SW)
/Regulators/vc: R90.1, U8.14 (VC)
GND: C44.2, C46.2, C47.2, C48.2, C49.2, C50.2, C52.2, C55.2, C57.2, C58.2, C61.2, C62.2, C65.2, C66.2, C67.2, C68.2, C72.2, C73.2, C74.2, C75.2, C76.2, C78.2, C79.2, C80.2, J7.1, Q1.2 (S), R85.2, R86.2, R89.2, R91.2, R92.2, R93.2, R104.2, R122.2, U7.5 (ILIM), U7.8 (GND), U7.11 (GND), U8.3 (GND), U8.4 (GND), U8.25 (GND), U8.26 (GND), U8.27 (GND), U8.28 (GND), U8.29 (GND), U8.30 (GND), U8.31 (GND), U8.32 (GND), U9.7 (200MV), U9.8 (GND), U9.10 (800MV), U9.18 (GND), U9.21 (GND_TH), U12.4 (GND), U12.5 (GND), U12.10 (RETRY_DLY), U12.12 (LDSTRT), U12.14 (GND), U12.26 (GND); also elsewhere on the board
unnamed: C48.1, R90.2
unnamed: D17.1 (K), R112.1
unnamed: Q1.3 (D), R112.2
unnamed: Q1.1 (G), R111.2, U7.3 (EN/UV), U8.18 (PG)
unnamed: C44.1, C47.1, L17.1, U7.1 (IN), U7.2 (IN), U7.6 (PGFB)
unnamed: C57.1, R93.1, U7.7 (SET)
unnamed: TP5.1, U8.20 (CLKOUT)
unnamed: R88.2, U8.10 (EN/UVLO)
unnamed: C62.1, U8.11 (INTVCC)
unnamed: R89.1, U8.19 (SYNC)
unnamed: C77.2, U9.3 (FB)
unnamed: C74.1, U9.13 (NR/SS)
unnamed: R86.1, U12.8 (ILIM)
unnamed: R122.1, U12.9 (IMON)

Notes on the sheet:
No Retry
50mA * (3.3v-1.8v) = 75mW
DAC AVDD Regulator Sequences on after +3.3v
15A Max
ADC IOVDD
Switching Frequency 2MHz
Logic Translator Regulator
Install R89 for Pulse Skipping Mode Remove for Forced Continuous Mode
Add ADC to Rimon to measure current
